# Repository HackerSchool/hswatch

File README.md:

# HSWatch

## Objective

This project aims to create a _diy_ smartwatch, open-source and programable using Arduino code style, so that hobbyists, students and hackers can contribute to this project and design their own smartwatch according to their tastes. Besides the watch it self this project also contains an Android companion app source code, that is also extendable so that the watch can accomodate more features.

## Features 

This are the features that are already implemented:
- Show a clock (hours, minutes, seconds, day, month, year, week day) regularly syncronized with the smartphone clock.
- Mirror notifications from the smartphone to the watch screen, vibrating each time a new one is received.
- Show notification history, blinking a RGB LED each time there is an unread message. (The LED blinks a diferent color for diferent types of notifications)
- Measure battery charge level of the smartwatch and show it on the main screen.
- Three adjustable alarm clocks. This alarms sound a buzzer and vibrate the watch.
- Stop watch and timer.
- Show 6 days weather forecast on watch screen, using the smartphone companion app as a gateway to online weather services.

The software was made to be easily extendable, feel free to add more features.

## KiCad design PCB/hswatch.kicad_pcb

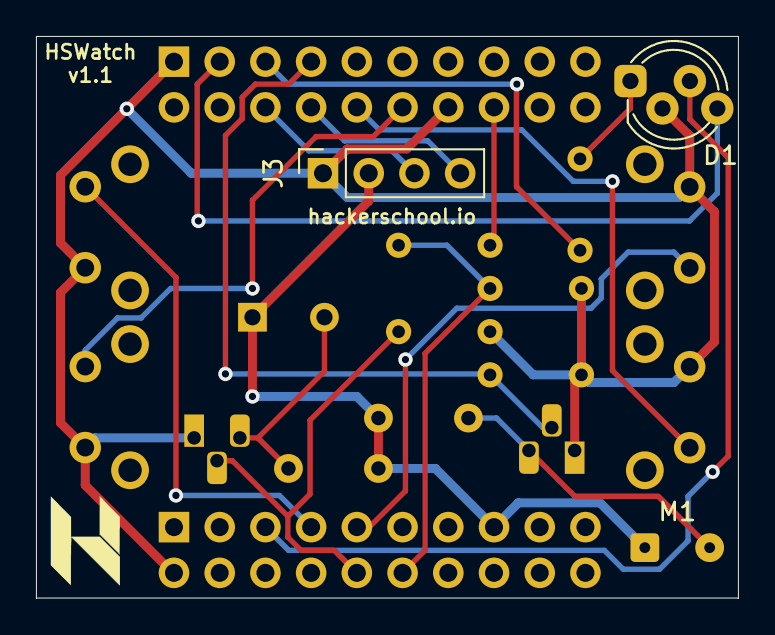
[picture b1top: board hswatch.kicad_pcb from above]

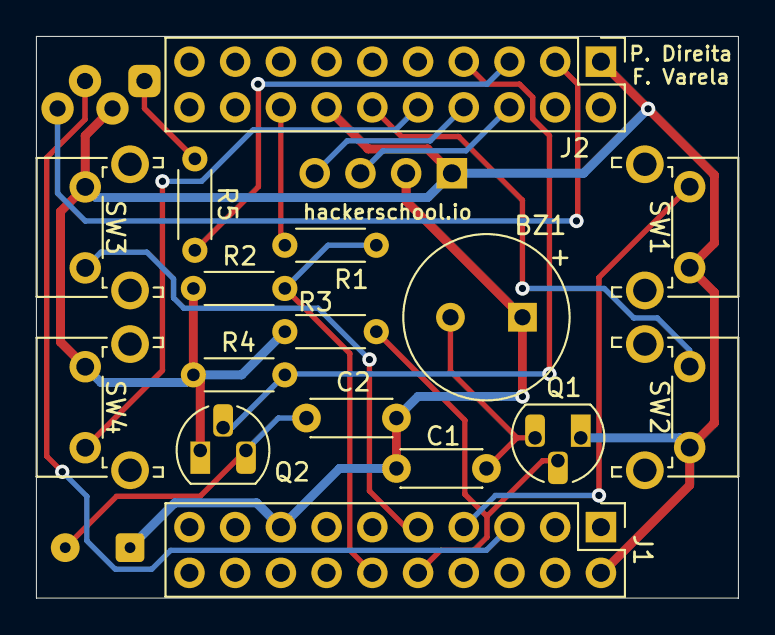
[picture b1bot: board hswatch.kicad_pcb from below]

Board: 2 copper layers, 39.0 x 31.2 mm, 19 parts (16 on the bottom side), 18 nets.

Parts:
BZ1: Buzzer; MagneticBuzzer_CUI_CST-931RP-A
C1, C2: 39p; C_Disc_D4.3mm_W1.9mm_P5.00mm
D1: LED_RGBC; LED_D5.0mm-4_RGB_Staggered_Pins
J1: Conn_02x10_Down; PinHeader_2x10_P2.54mm_Vertical
J2: Conn_02x10_Up; PinHeader_2x10_P2.54mm_Vertical
J3: Conn_Oled_Disp; PinSocket_1x04_P2.54mm_Vertical
M1: Vibrator_Motor; SolderWire-0.1sqmm_1x02_P3.6mm_D0.4mm_OD1mm
Q1, Q2: 2N7000; TO-92_HandSolder
R1, R2: 47k; R_Axial_DIN0204_L3.6mm_D1.6mm_P5.08mm_Horizontal
R3, R4: 100k; R_Axial_DIN0204_L3.6mm_D1.6mm_P5.08mm_Horizontal
R5: 100; R_Axial_DIN0204_L3.6mm_D1.6mm_P5.08mm_Horizontal
SW1: SW_Push_Up_Left; SW_Tactile_SPST_Angled_PTS645Vx83-2LFS
SW2: SW_Push_Down_Left; SW_Tactile_SPST_Angled_PTS645Vx83-2LFS
SW3: SW_Push_Up_Right; SW_Tactile_SPST_Angled_PTS645Vx83-2LFS
SW4: SW_Push_Down_Right; SW_Tactile_SPST_Angled_PTS645Vx83-2LFS

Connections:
/b_d_l: J2.12, SW2.1
/b_d_r: J2.10, SW4.1
/b_u_l: J1.7, SW1.1
/b_u_r: J1.9, SW3.1
/buzzer: J1.10, Q1.2, R3.1
/led_b: D1.3, J1.5
/led_g: D1.4, J2.3
/led_r: J2.5, R5.2
/mes_bat: J1.12, R1.2, R2.1
/scl: J2.6, J3.3
/sda: J2.8, J3.4
/v_bat: J2.16, R1.1
/vibrator: J2.7, Q2.2, R4.1
GND: D1.2, J1.2, J2.1, J2.14, J3.1, Q1.1, Q2.1, R2.2, R3.2, R4.2, SW1.2, SW2.2, SW3.2, SW4.2
unnamed: BZ1.2, C1.2, Q1.3
unnamed: C2.2, M1.2, Q2.3
unnamed: D1.1, R5.1
VDD: BZ1.1, C1.1, C2.1, J1.15, J3.2, M1.1

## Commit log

2018-05-14 HsWatch first commit - Testes BT, Material
    -> Documentos do Projecto com o material necessario e breve descrição
    -> Set-up da comunicação entre o modulo bluetooth e o arduino, sofware para o Arduino que permite fazer de repetidor bluetooth
2018-06-11 Attempt to connect to github
2018-06-11 Android App for connecting to bluetooth - Everything in Main
2018-06-11 Documentação da library do display
    Documentação oficial da adafruit para a library "Adafruit GFX Library"
2018-11-26 Teste do ESP32
2018-11-27 Melhor nome para a repo partihada
2018-12-02 LED a piscar por Bluetooth
2018-12-02 Nova organização das libs e texto sobre BLE
2019-08-08 Major developmente in HSwatch project
    Core files of the ESP32 watch OS were uploaded. Issues found on the multithread capability of the OLED display library.
2019-08-10 Change of the display library
    The display library was changed to the thingpulse library instead of the adafruit one, however there is still issues regarding to the multithreading capability of the display library. This may be due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
2019-08-16 Multithread capability of display library added
    The main thread handles the display and receives requests from other threads through a queue. All the display library was reimplemented in order to cope with that queue.
2019-08-20 Add timer functionality
    Clock is already working, and can be updated via bluetooth. The system is prepared to receive other apps that need to have a notion of time.
2020-03-20 Add notification icons to the main screen & bug fixes
2020-03-20 Display was made thread safe
2020-03-20 Add button functionality
2020-03-21 Add ability to review each notification through the notification app
2020-03-26 Create HSWatch's app folder
2020-03-26 Adding Android's files
2020-03-26 Changing README
2020-03-27 Criado o fragmento principal
    Foi criado o fragmento principal onde tem como função mostrar as funcionalidades e estado que a app pode dar ao relógio. Falta reorginazação da atividade.
2020-03-27 Progress in main fragment
2020-03-29 Progress in the setup fragments
    It was created and builded the fragments which can setup the conection Bluetooth. Next step is to build the connection's Service.
2020-03-29 Conection's Thread implemented
2020-03-29 Make the fragments more fluid
2020-04-02 Make notifications, in the notification list erasable. Define protocol for weather app
2020-04-03 Create main menu
    Main menu tested
    timer and alarm app logos created
2020-04-03 Service and notifications prepared (sync time)
2020-04-03 Fixed bug about sync time
2020-04-04 Timer App added & Several minor changes to make the code more modular
    In fact the App is called Chronograph & Timer, because it is able to simultaneusly do those two funcions.
2020-04-07 Add Vibration functionality
2020-04-08 Add Buzzer functionality
2020-04-10 Now it is possible to maintain a connection. MainActivity new design.
2020-04-13 Weather API Implementation
2020-04-13 Adding PT Cities JSON file
2020-04-16 Add API functionality's and Settings Activity
2020-05-04 Add Alarm functionality
2020-05-04 Add to the main screen alarm icon
2020-05-04 Bug fix, show alarm icon main screen
2020-05-04 Testing NotificationListener
2020-05-06 Add weather app
    Additional changes to the protocol were made
2020-05-08 Add led functionality and update to weather app
    In additation small changes were made the bluetooth communication library in order to make it more robust.
2020-05-08 Adding the connection listeners for the notification listener
2020-05-09 Update the app
2020-05-11 Change notification app to support notifying action
2020-05-11 The way that notifications are erased was changed
2020-05-11 Change the API implementation (adding the time interval to call API)
    Now the user is waiting 3 hours to get new information about the weather.
2020-05-11 Update Servico.java - added writting file and the file
2020-05-12 Led module complete
    The notification app makes use of the led module fade function having a diferent color for each type of notification
2020-05-12 watch firmware directory reorganize
2020-05-12 Bug fix
2020-05-12 Test: Notifications
2020-05-12 Adding check on listenerDisconnect
2020-05-13 API is implemented correctly this time. It needs to specify the city tho.
2020-05-16 Change the icon line in profile
2020-05-16 Change to Int to Double in profile
2020-05-16 Removed the toast notifications
2020-05-19 Add battery level and bt connection indicator functionality
2020-05-19 Add vibration when notification is received
2020-06-11 Change led pinout
2020-08-04 Android Update
2020-09-27 Implemented the reading Notifications, SMS's, Calls functions and the scheduled sending the time task
2020-09-27 Testing the commit changes
2020-09-27 Correcting commit modifications
2020-12-06 Added a dummy notification
2020-12-06 Small diferences in the dummy not
    May have problems in the weather, because of the transiction to adding the GPS function
2020-12-07 Update to battery library to adapt to TTGO T7 v1.3 board
2020-12-22 The GPS Switch is workjing as it should - OFF = Choosen City
2020-12-22 GPS Listener and functionality added
2021-02-02 Calibrate battery measurement system
2021-02-02 Clean up project directory
2021-02-02 Add HSWatch picture
2021-03-21 Added 3D_Models directory
    * With 3D model for the case and internal circuits
2021-03-24 Made enclosure of the 3d model
2021-03-24 Surpass conflict on Case:_Side_Left file
2021-03-24 Update case cover
2021-03-24 Added Steps
2021-03-24 Create Assembly of hswatch & fix modeling issues
2021-03-25 Update Assembly 3D
2021-03-26 New version of 3D model
    Stronger bracelet support, prettier design
2021-03-26 3D model, design incompatibilities fixes
2021-03-30 Update of 3D model, small details to make the model fit better with the rest of the system
2021-04-03 First Refactor
2021-04-07 Bug fix on the change month logic
2021-04-10 Initial Update
2021-04-10 Finish the seting up the bluetooth connection
2021-04-10 Added some documentation
2021-04-10 Change the Servico name to MainServico, refactor it and added to the manifest file
2021-04-10 Added some last changes for the day
2021-04-15 Add little changes
2021-04-15 Fix some errors on the connection, but still under maintainance
2021-04-17 Connection to the hswatch recreated and refactored
2021-04-22 Beginning of ReconnectionWorker
2021-04-23 First interation to the bluetooth device reconection
    Need tests to garantee that this method works
2021-04-24 Perfect it the documentation and code structure
2021-04-24 Added flagError to prevent the connection to proceed
2021-04-24 Update streams initializations and test it the broadcast receiver for within range connections
2021-04-24 Update files to work on "Sobre" on the Main Activity
2021-04-25 Added the "About" section
2021-04-29 Led library updates
    Supports prioritizing of led tasks. Now a new led task cancels the previous if its high priority or its ignored otherwise instead of being put in a waiting list
2021-04-30 Add Flashligh app and fix minor bugs in led library
    Some changes were also made in the color of the led blinking in notifications
2021-05-01 Corrected a bit of the README
2021-05-06 Refactor how the notifications are sent to the service.
    Still needs some lines to be fulle refactor, but now is working as it should be
2021-05-08 Add settings app and modify device libraries
2021-05-08 Add About app
2021-06-06 Reconnection done! Close #11
2021-06-06 Clean some classes and rearrange files
2021-06-06 Prepare for notifications filter
2021-06-07 createConnection method more independent and code cleaning
2021-06-20 Notification Filter first iteration version
2021-06-29 Added a thread to test the connection in every 30 seconds
2021-06-29 Added the project logo to the app (#14)
2021-06-29 Start layout design refactoring
    * Added configuration master to control the rest of the setup fragments;
    * Added the setup fragment, but it needs to finish the layout
2021-06-30 Setup Start Fragment finished (#12)
2021-07-01 Some changes to the setup fragment ( #12 & #14)
2021-07-01 Added the setup service fragment ( #12 & #14 )
2021-07-02 Rearrange the layout on the start seetup fragment ( #14 )
2021-07-02 Setup service fragment implemented ( #12 & #14 )
2021-07-17 Fixed the BackButton on the Setup Configuration Fragments ( Closed #15 )
2021-07-17 All the setup fragments done. Tests are needed though. ( #14 )
2021-07-19 Setup animations finish ( #14 )
    There is still needs a initial fragment stup for the first time opening the app
2021-07-19 Some touches in the connection side of the layout ( #14 #12 )
2021-07-19 Some touches to the connection side ( #16 #12 )
2021-07-21 Connection stablished and finished ( Close #16 , Close #12 )
2021-07-21 Trace one test run
2021-07-23 App ready for the first deployment ( Close #17 & Close #16 & Close #14 & Close #12 )
    Possible it should have many commits accumulated on this one, but vacations were in the way and I completely forgot. My apologies for any inconvinience!
2021-07-23 Clean some unused files
2021-07-23 Fix some errors occured by the cleaning made on the previous commit
2021-08-01 Add vibrator adaptor
2021-08-03 Increase catilever size
2021-08-03 Added the bundle/apk signed files to deploy the app
2021-08-29 Change screen hole size in 3D model
2021-12-27 Android section build files
2021-12-30 API Key and Connection Switch fixed (Closes #19 )
    Now the API Key is requested to the user and tested if it works.
    Aswell the connection switch now tell exactly if there is a connection or not.
2022-05-15 Add documentation images
2022-05-18 Android Studio Update
    Added the files modified by the current Android Studio's update
2022-05-18 HSWatch Connection Module Added
    It was implemented the HSWatch Connection Module, the module that will be used in the Workshops and/or as dependency for projects similar of this one.
    The idea behind it was to make the connection part (the most complex one) as modular as possible within the project context and to make this section as independent as possible so it could be used in 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
2022-05-18 Dependencies updated
    Some of the Android dependencies were updated, with the application working just fine without the connection just yet. If there is a problem with respect to that, an issue will be created to handle t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
2022-05-19 Android Manifest updated to the current compileSDK version
    Since there were some changes in the previous commit in respect of the dependencies version, the manifest was necessary to change to adjust those changes, which was not committed up until now.
    Hopefully, these changes solve this problem and the following commits will be just the advance of the module.
2022-05-23 Update 3D model folder
2022-05-29 Update library dependencies
2022-05-30 Include vector library
2022-05-30 Add flash firmware and user manual images to documentation
2022-06-06 Add quotes image
2022-06-06 Add Quotes App
2022-06-07 Add Exterior images of HSWatch
2022-06-07 Add PCB design
2022-06-07 HSWatch connection submodule implemented
    The submodule for the bluetooth connection is now complete and ready for tests. Therefore, this submodule will be, ideally, a gitsubmodule of a repository, which will make, possibly, in the future co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
    As for the main changes in this commit. This one is just a collective addition and copying of existing files from the bluetooth connection - such as MainService (now HSWService in the submodule) or t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
2022-06-07 Fix LED crashing when turning off
2022-06-07 Fix sending time to watch on locales other than pt
2022-06-07 Fix month being zero-based
2022-07-06 Update the app for release
2022-07-06 Fix some portuguese errors
2022-07-06 Updated the .gitignore in the Android folder
2022-07-06 Removed the release folder in the Android section
